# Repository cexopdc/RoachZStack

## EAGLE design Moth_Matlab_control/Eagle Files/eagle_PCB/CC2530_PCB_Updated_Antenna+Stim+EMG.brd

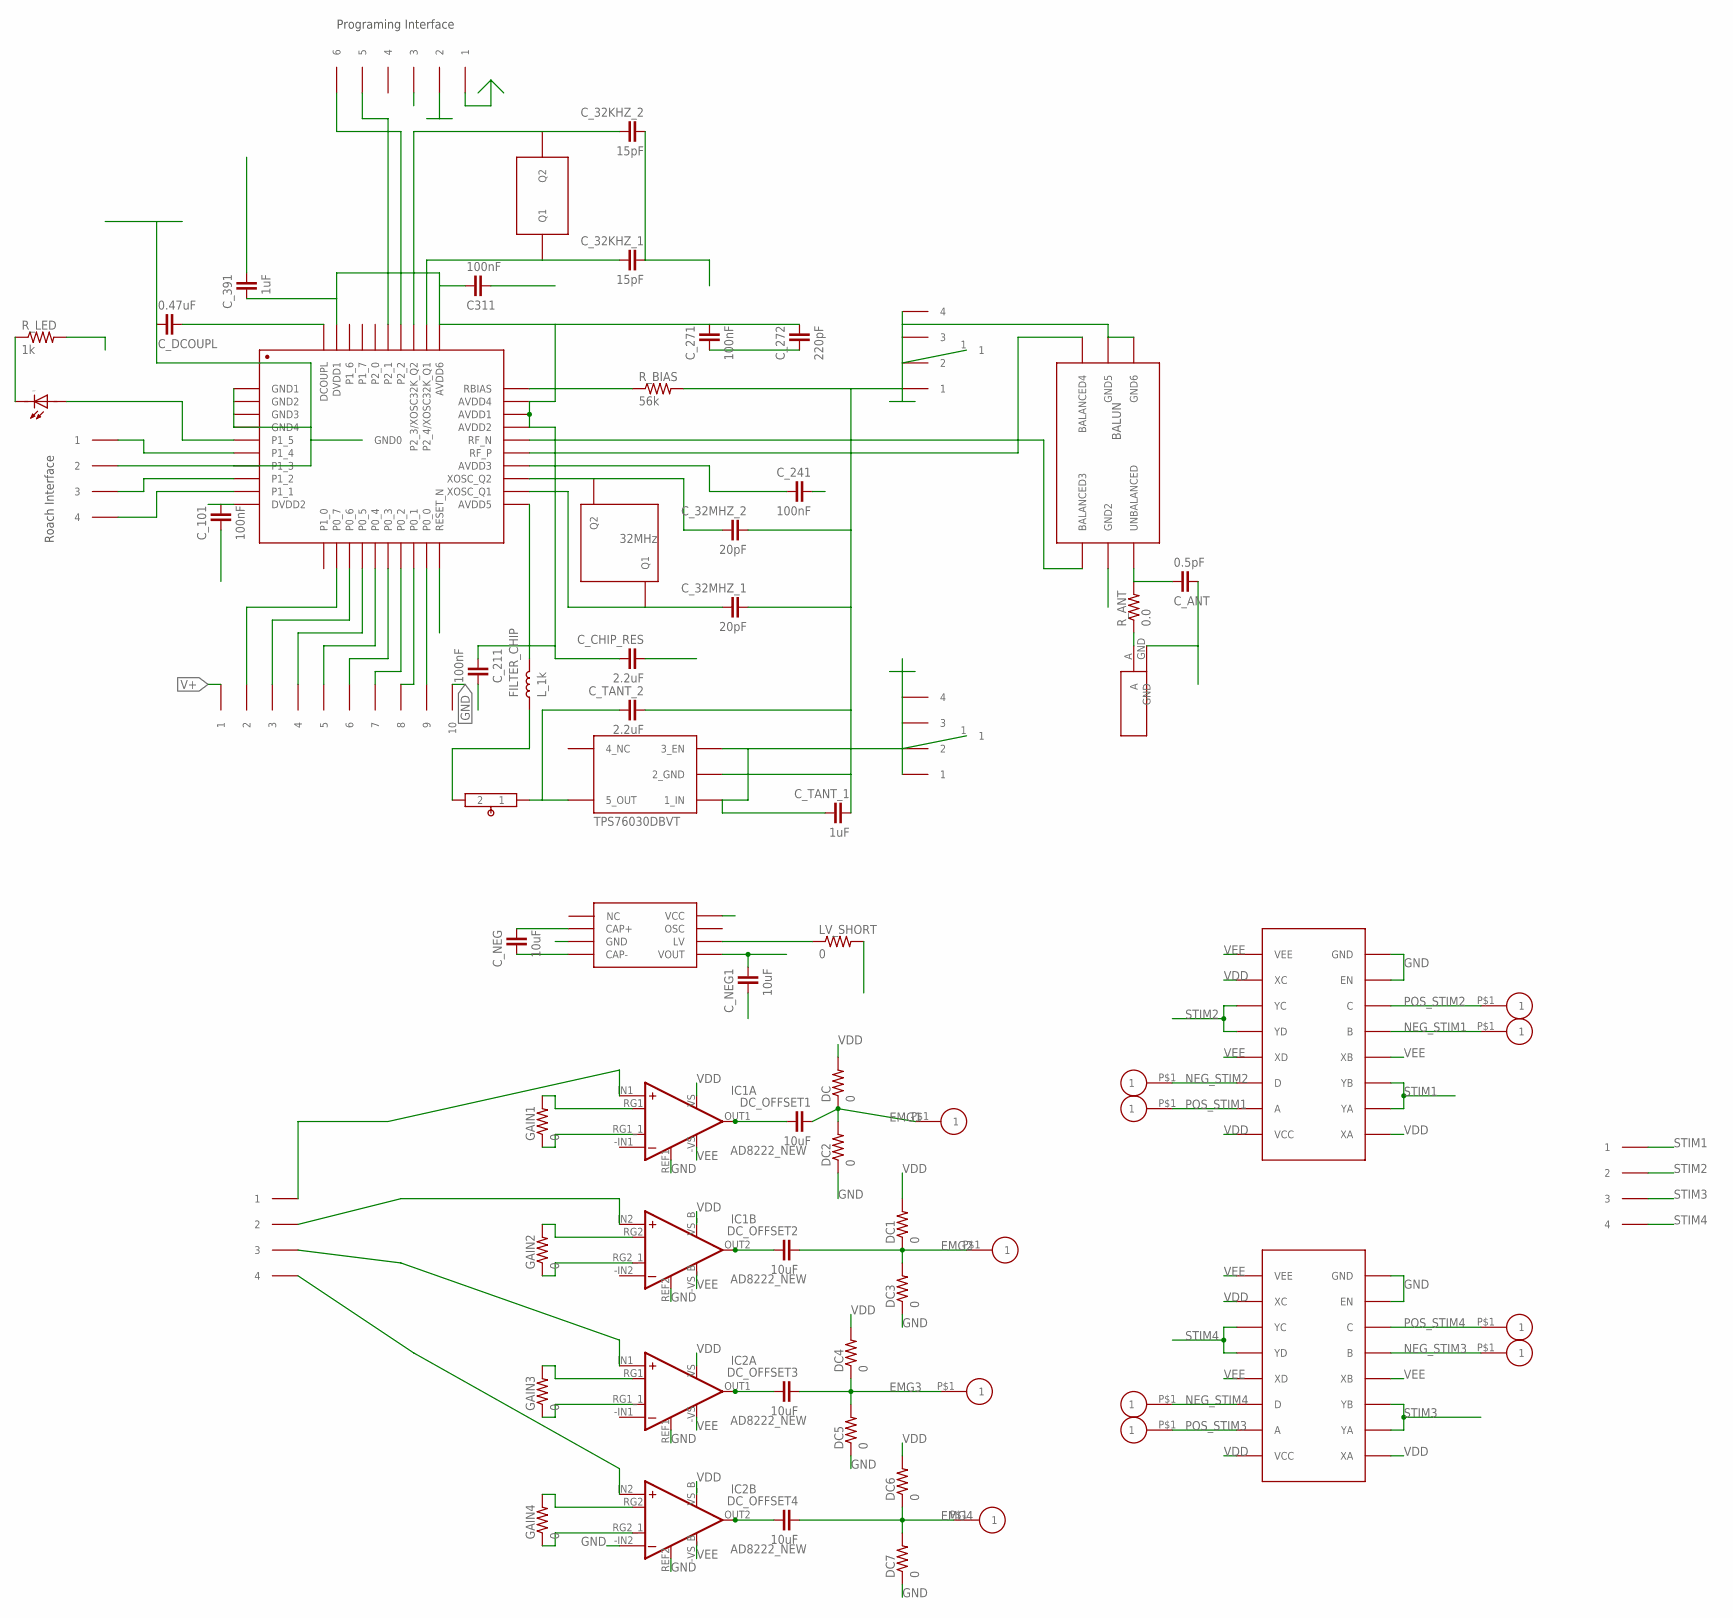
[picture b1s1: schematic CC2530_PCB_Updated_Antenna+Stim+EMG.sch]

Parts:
32KHZ: X32.768KHZ
C311: 100nF; 0201_R/L/C
C_32KHZ_1, C_32KHZ_2: 15pF; 0201_R/L/C
C_32MHZ_1, C_32MHZ_2: 20pF; 0201_R/L/C
C_101, C_211, C_241, C_271: 100nF; 0201_R/L/C
C_272: 220pF; 0201_R/L/C
C_391: 1uF; 0201_R/L/C
C_ANT: 0.5pF; 0201_R/L/C
C_CHIP_RES: 2.2uF; 0402_R/L/C
C_DCOUPL: 0.47uF; 0201_R/L/C
C_NEG, C_NEG1: 10uF; 0402_R/L/C
C_TANT_1: 1uF; 0603_R/L/C
C_TANT_2: 2.2uF; 0603_R/L/C
DC, DC1, DC2, DC3, DC4, DC5, DC6, DC7: 0; 0402_R/L/C
DC_OFFSET1, DC_OFFSET2, DC_OFFSET3, DC_OFFSET4: 10uF; 0402_R/L/C
EMG1: DBG_ELECTRODE
FILTER_CHIP: L_1k; 0402_R/L/C
GAIN1, GAIN2, GAIN3, GAIN4: 0; 0402_R/L/C
GND_IN: FFC4POS
IC1, IC2: AD8222_NEW; QFN-16
INVERTED_F-ANTENNA: ANTENNA
LED: LED0603; 0603_R/L/C
LV_SHORT: 0; 0402_R/L/C
R_ANT: 0.0; 0201_R/L/C
R_BIAS: 56k; 0201_R/L/C
R_LED: 1k; 0402_R/L/C
U$1: CC2530
U$2: BALUN
U$3: X32MHZ
U$4: TL7660; S-PDSO-G8
U$5, U$6: MC74HC4316A; SOIC-16-ON-SEMI
U$9, U$11, U$12, U$14, U$16, U$19, U$22, U$23, U$25, U$26, U$27: DBG_ELECTRODE
U$10: REGULATOR
U$13, U$24, U$28: FFC4POS
U$15: FFC10POS
U$17: FFC6POS
U$18: SWITCH_MANUAL
V+_IN: FFC4POS
WIRE+: DRILL_CONNECT
WIRE-: DRILL_CONNECT

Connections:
DCOUPL1: C_DCOUPL.1, U$1.DCOUPL
EMG1: DC.1, DC2.2, DC_OFFSET1.2, EMG1.P$1
EMG2: DC1.1, DC3.2, DC_OFFSET2.2, U$25.P$1
EMG3: DC4.1, DC5.2, DC_OFFSET3.2, U$26.P$1
EMG4: DC6.1, DC7.2, DC_OFFSET4.2, U$27.P$1
GND: C311.1, C_32KHZ_1.2, C_32KHZ_2.2, C_32MHZ_1.2, C_32MHZ_2.2, C_101.1, C_211.2, C_241.2, C_271.1, C_272.1, C_391.2, C_ANT.1, C_CHIP_RES.2, C_DCOUPL.2, C_NEG1.1, C_TANT_1.2, C_TANT_2.2, DC2.1, DC3.1, DC5.1, DC7.1, GND_IN.1, GND_IN.2, GND_IN.3, GND_IN.4, IC1.REF1 (REF), IC1.REF2 (REF), IC2.-IN2 (-IN), IC2.REF1 (REF), IC2.REF2 (REF), INVERTED_F-ANTENNA.GND, LV_SHORT.2, R_BIAS.2, R_LED.2, U$1.GND0, U$1.GND1, U$1.GND001 (GND0), U$1.GND2, U$1.GND002 (GND0), U$1.GND3, U$1.GND003 (GND0), U$1.GND4, U$1.GND004 (GND0), U$1.GND005 (GND0), U$1.GND006 (GND0), U$1.GND007 (GND0), U$1.GND008 (GND0), U$1.GND009 (GND0), U$1.GND010 (GND0), U$1.GND011 (GND0), U$1.GND012 (GND0), U$1.GND013 (GND0), U$1.GND014 (GND0), U$1.GND015 (GND0), U$1.GND016 (GND0), U$1.P1_3, U$2.GND2, U$2.GND5, U$2.GND6, U$4.3 (GND), U$5.7 (EN), U$5.8 (GND), U$6.7 (EN), U$6.8 (GND), U$10.2 (2_GND), U$13.2, U$15.10, U$17.2, WIRE-.1
LED/P1_5: LED.1 (A), U$1.P1_5
LT/P1_4: U$1.P1_4, U$13.1
unnamed: C_ANT.2, R_ANT.2, U$2.UNBALANCED
unnamed: INVERTED_F-ANTENNA.A, R_ANT.1
unnamed: C_NEG.2, U$4.2 (CAP+)
unnamed: C_NEG.1, U$4.4 (CAP-)
unnamed: LV_SHORT.1, U$4.6 (LV)
unnamed: GAIN1.2, IC1.RG1
unnamed: GAIN1.1, IC1.RG1_1
unnamed: GAIN2.2, IC1.RG2 (RG1)
unnamed: GAIN2.1, IC1.RG2_1 (RG1_1)
unnamed: GAIN3.2, IC2.RG1
unnamed: GAIN3.1, IC2.RG1_1
unnamed: GAIN4.2, IC2.RG2 (RG1)
unnamed: GAIN4.1, IC2.RG2_1 (RG1_1)
unnamed: DC_OFFSET1.1, IC1.OUT1 (OUT)
unnamed: DC_OFFSET2.1, IC1.OUT2 (OUT)
unnamed: DC_OFFSET4.1, IC2.OUT2 (OUT)
unnamed: DC_OFFSET3.1, IC2.OUT1 (OUT)
unnamed: IC2.IN2 (+IN), U$24.4
unnamed: IC2.IN1 (+IN), U$24.3
unnamed: IC1.IN2 (+IN), U$24.2
unnamed: C_TANT_2.1, U$10.5 (5_OUT), U$18.1
unnamed: IC1.IN1 (+IN), U$24.1
unnamed: LED.2 (C), R_LED.1
NC: U$4.1 (NC)
NEG_STIM1: U$5.5 (B), U$14.P$1
NEG_STIM2: U$5.14 (D), U$9.P$1
NEG_STIM3: U$6.5 (B), U$19.P$1
NEG_STIM4: U$6.14 (D), U$22.P$1
OSC: U$4.7 (OSC)
P0_0: U$1.P0_0, U$15.9
P0_1: U$1.P0_1, U$15.8
P0_2: U$1.P0_2, U$15.7
P0_3: U$1.P0_3, U$15.6
P0_4: U$1.P0_4, U$15.5
P0_5: U$1.P0_5, U$15.4
P0_6: U$1.P0_6, U$15.3
P0_7: U$1.P0_7, U$15.2
P2_1: U$1.P2_1, U$17.5
P2_2: U$1.P2_2, U$17.6
P2_3/X32K_Q2: 32KHZ.Q2, C_32KHZ_2.1, U$1.P2_3/XOSC32K_Q2
P2_4/X32K_Q1: 32KHZ.Q1, C_32KHZ_1.1, U$1.P2_4/XOSC32K_Q1
POS_STIM1: U$5.15 (A), U$11.P$1
POS_STIM2: U$5.6 (C), U$12.P$1
POS_STIM3: U$6.15 (A), U$23.P$1
POS_STIM4: U$6.6 (C), U$16.P$1
RBIAS: R_BIAS.1, U$1.RBIAS
RESET: U$1.RESET_N, U$17.3
RF_N: U$1.RF_N, U$2.BALANCED3
RF_P: U$1.RF_P, U$2.BALANCED4
RT/P1_2: U$1.P1_2, U$13.3
STIM1: U$5.2 (YA), U$5.3 (YB), U$28.1
STIM2: U$5.11 (YC), U$5.12 (YD), U$28.2
STIM3: U$6.2 (YA), U$6.3 (YB), U$28.3
STIM4: U$6.11 (YC), U$6.12 (YD), U$28.4
SWITCH_OUT: FILTER_CHIP.1, U$18.2
UP/P1_1: U$1.P1_1, U$13.4
V+: C_TANT_1.1, U$10.1 (1_IN), U$10.3 (3_EN), U$15.1, V+_IN.1, V+_IN.2, V+_IN.3, V+_IN.4, WIRE+.1
VDD: C311.2, C_101.2, C_211.1, C_241.1, C_271.2, C_272.2, C_391.1, C_CHIP_RES.1, DC.2, DC1.2, DC4.2, DC6.2, FILTER_CHIP.2, IC1.VS (V+), IC1.VS_B (V+), IC2.VS (V+), IC2.VS_B (V+), U$1.AVDD1, U$1.AVDD2, U$1.AVDD3, U$1.AVDD4, U$1.AVDD5, U$1.AVDD6, U$1.DVDD1, U$1.DVDD2, U$4.8 (VCC), U$5.1 (XA), U$5.10 (XC), U$5.16 (VCC), U$6.1 (XA), U$6.10 (XC), U$6.16 (VCC), U$17.1
VEE: C_NEG1.2, IC1.-VS (V-), IC1.-VS_B (V-), IC2.-VS (V-), IC2.-VS_B (V-), U$4.5 (VOUT), U$5.4 (XB), U$5.9 (VEE), U$5.13 (XD), U$6.4 (XB), U$6.9 (VEE), U$6.13 (XD)
X32M_Q1: C_32MHZ_1.1, U$1.XOSC_Q1, U$3.Q1
X32M_Q2: C_32MHZ_2.1, U$1.XOSC_Q2, U$3.Q2

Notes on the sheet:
Programing Interface
Roach Interface

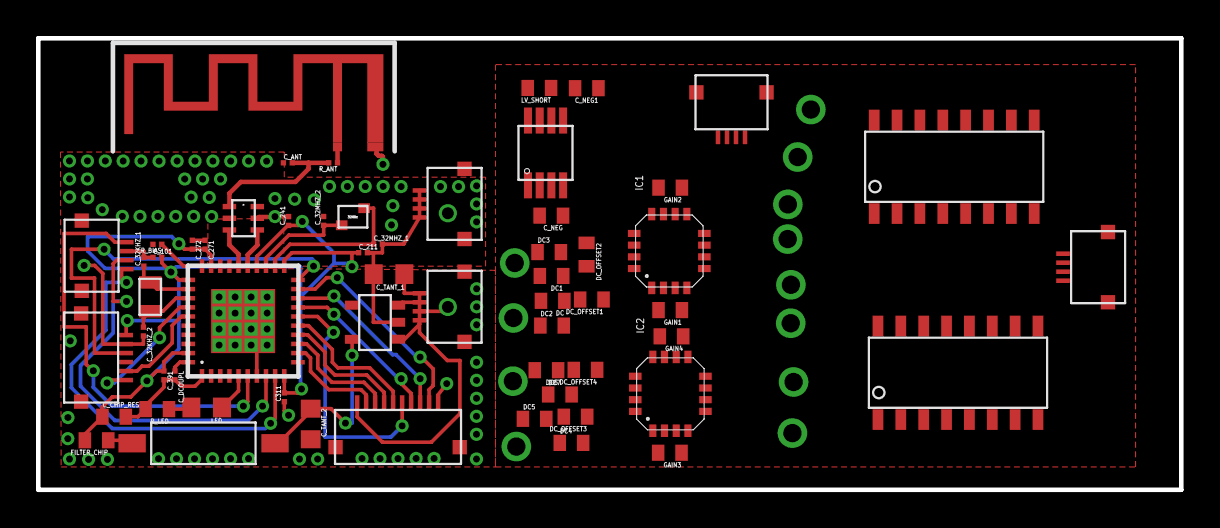
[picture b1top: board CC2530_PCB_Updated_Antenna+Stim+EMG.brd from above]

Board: 2 copper layers, 63.5 x 25.1 mm, 73 parts (0 on the bottom side), 67 nets.

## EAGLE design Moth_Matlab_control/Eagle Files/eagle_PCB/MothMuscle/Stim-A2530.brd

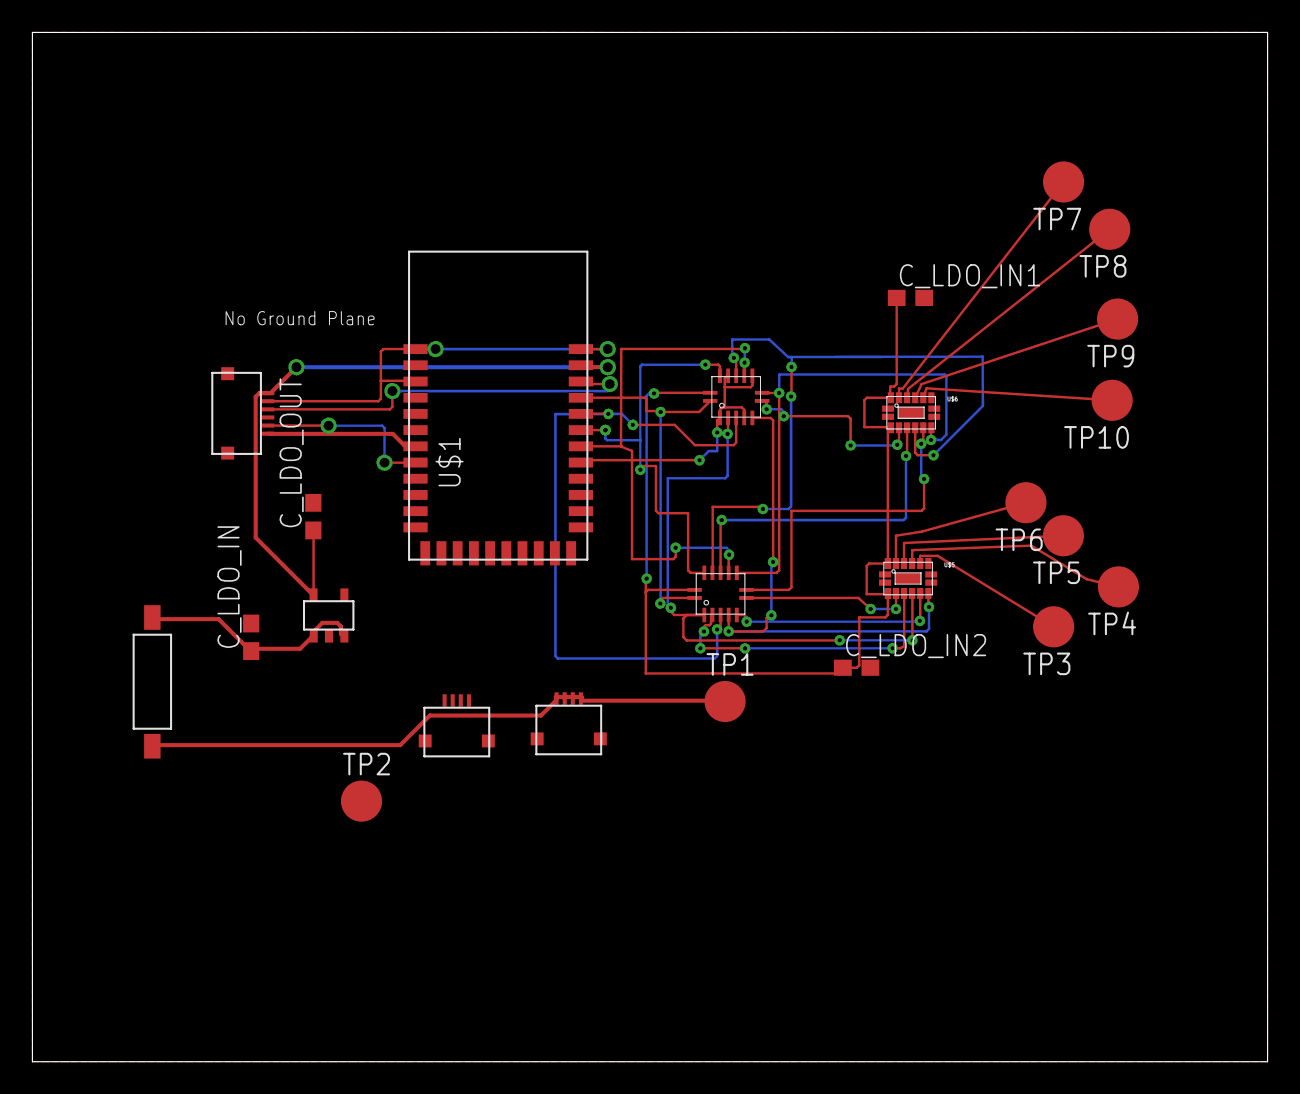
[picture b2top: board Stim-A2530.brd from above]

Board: 2 copper layers, 76.2 x 63.5 mm, 24 parts (0 on the bottom side), 29 nets.

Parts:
C_LDO_IN: 1uF; C0603
C_LDO_IN1, C_LDO_IN2: .1uF; C0603
C_LDO_OUT: 2.2uF; C0603
TP1, TP2, TP3, TP4, TP5, TP6, TP7, TP8, TP9, TP10: PTR1B2,54; B2,54
U$1: A2530
U$2: FFC6POS
U$3: AND_QUAD; QFN-14
U$4: XOR_QUAD; QFN-14
U$5, U$6: DRV8835; QFN-12-HEATSINK
U$7, U$8: FFC4POS
U$18: SWITCH_MANUAL
VREG1: REGULATOR

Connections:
+3V0: C_LDO_OUT.1, U$1.P$33, U$2.1, VREG1.5
+3V3: C_LDO_IN1.1, C_LDO_IN2.1, U$3.VCC, U$4.VCC, U$5.VCC, U$5.VM, U$6.VCC, U$6.VM
BCLK: U$1.P$27, U$3.B0, U$3.B1, U$3.B2, U$3.B3
GND: C_LDO_IN.2, C_LDO_IN1.2, C_LDO_IN2.2, C_LDO_OUT.2, TP2.TP, U$1.P$1, U$1.P$3, U$1.P$12, U$1.P$13, U$1.P$14, U$1.P$15, U$1.P$22, U$1.P$34, U$2.2, U$3.GND, U$4.GND, U$5.GND, U$5.MODE, U$6.GND, U$6.MODE, U$8.1, U$8.2, U$8.3, U$8.4, VREG1.2
unnamed: TP1.TP, U$7.1, U$7.2, U$7.3, U$7.4, U$18.1
unnamed: TP7.TP, U$6.AOUT1
unnamed: TP8.TP, U$6.AOUT2
unnamed: TP9.TP, U$6.BOUT1
unnamed: TP10.TP, U$6.BOUT2
unnamed: TP6.TP, U$5.AOUT1
unnamed: TP5.TP, U$5.AOUT2
unnamed: TP4.TP, U$5.BOUT1
unnamed: TP3.TP, U$5.BOUT2
NEG1: U$3.O_0, U$4.B0, U$5.AIN2.AENBL
NEG2: U$3.O1, U$4.B1, U$5.BIN2/BENBL
NEG3: U$3.O2, U$4.B2, U$6.AIN2.AENBL
NEG4: U$3.O3, U$4.B3, U$6.BIN2/BENBL
P1: U$1.P$31, U$3.A0, U$4.A0
P2: U$1.P$30, U$3.A1, U$4.A1
P2_1: U$1.P$8, U$2.5
P2_2: U$1.P$7, U$2.6
P3: U$1.P$29, U$3.A2, U$4.A2
P4: U$1.P$28, U$3.A3, U$4.A3
POS1: U$4.O_0, U$5.AIN1/APHASE
POS2: U$4.O1, U$5.BIN1/BPHASE
POS3: U$4.O2, U$6.AIN1/APHASE
POS4: U$4.O3, U$6.BIN1/BPHASE
RESET_N: U$1.P$32, U$2.3
V+: C_LDO_IN.1, U$18.2, VREG1.1, VREG1.3

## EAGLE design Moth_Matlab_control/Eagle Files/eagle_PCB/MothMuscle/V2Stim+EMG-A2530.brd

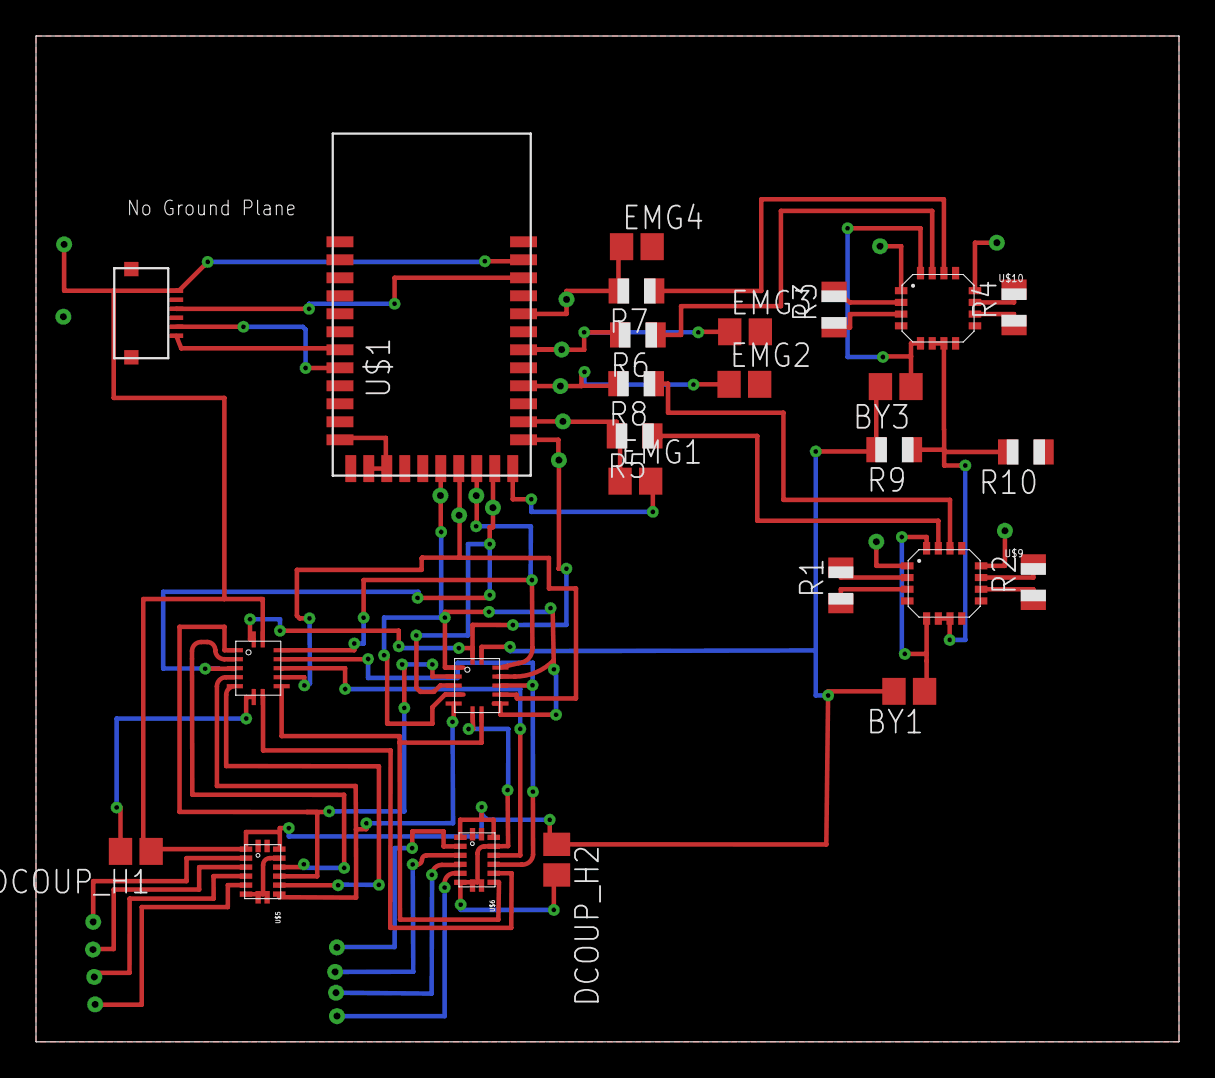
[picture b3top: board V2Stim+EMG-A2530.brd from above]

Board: 2 copper layers, 63.5 x 55.9 mm, 49 parts (0 on the bottom side), 49 nets.

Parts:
BY1, BY3: .1uF; C0805
DCOUP_H1, DCOUP_H2: .1uF; C0805
EMG1, EMG2, EMG3, EMG4: .1uF; C0805
R1, R2, R3, R4, R5, R6, R7, R8: 499; R0805
R9, R10: 10k; R0805
U$1: A2530
U$2: FFC6POS
U$3: AND_QUAD; QFN-14
U$4: XOR_QUAD; QFN-14
U$5, U$6: DRV8835; QFN-12-HEATSINK
U$7, U$8, U$11, U$12, U$13, U$14, U$15, U$16, U$17, U$18, U$19, U$20, U$21, U$22, U$23, U$24, U$25, U$26, U$27, U$28, U$29, U$30, U$31: DEBUG_PIN
U$9, U$10: AD8222; QFN-16

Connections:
+3V0: BY1.2, BY3.2, DCOUP_H1.1, DCOUP_H2.1, R9.2, U$1.P$33, U$2.1, U$3.VCC, U$4.VCC, U$5.VCC, U$5.VM, U$6.VCC, U$6.VM, U$26.P$1
A0: U$5.AOUT1, U$13.P$1
A1: U$5.AOUT2, U$14.P$1
B0: U$5.BOUT1, U$15.P$1
B1: U$5.BOUT2, U$16.P$1
BCLK: U$1.P$18, U$3.B0, U$3.B1, U$3.B2, U$3.B3, U$24.P$1
C0: U$6.AOUT1, U$17.P$1
C1: U$6.AOUT2, U$18.P$1
D0: U$6.BOUT1, U$19.P$1
D1: U$6.BOUT2, U$20.P$1
EMG1: EMG1.1, R5.2, U$1.P$24, U$31.P$1
EMG2: EMG2.1, R8.2, U$1.P$26, U$30.P$1
EMG3: EMG3.1, R6.2, U$1.P$28, U$29.P$1
EMG4: EMG4.1, R7.2, U$1.P$30, U$28.P$1
GND: DCOUP_H1.2, DCOUP_H2.2, EMG1.2, EMG2.2, EMG3.2, EMG4.2, R10.1, U$1.P$1, U$1.P$3, U$1.P$12, U$1.P$13, U$1.P$14, U$1.P$15, U$1.P$22, U$1.P$34, U$2.2, U$3.GND, U$4.GND, U$5.GND, U$5.MODE, U$6.GND, U$6.MODE, U$9.-VS, U$9.-VS_B, U$9.IN1, U$9.IN2, U$10.-VS, U$10.-VS_B, U$10.IN1, U$10.IN2, U$27.P$1
IN1: U$7.P$1, U$9.-IN1
IN2: U$8.P$1, U$9.-IN2
IN3: U$10.-IN1, U$11.P$1
IN4: U$10.-IN2, U$12.P$1
unnamed: R1.2, U$9.RG1
unnamed: R1.1, U$9.RG1_B
unnamed: R2.2, U$9.RG2
unnamed: R2.1, U$9.RG2_B
unnamed: R3.2, U$10.RG1
unnamed: R3.1, U$10.RG1_B
unnamed: R4.2, U$10.RG2
unnamed: R4.1, U$10.RG2_B
unnamed: R5.1, U$9.OUT1
unnamed: R8.1, U$9.OUT2
unnamed: R6.1, U$10.OUT1
unnamed: R7.1, U$10.OUT2
unnamed: BY3.1, U$10.VS, U$10.VS_B
unnamed: BY1.1, U$9.VS, U$9.VS_B
NEG1: U$3.O_0, U$4.B0, U$5.AIN2
NEG2: U$3.O1, U$4.B1, U$5.BIN2
NEG3: U$3.O2, U$4.B2, U$6.AIN2
NEG4: U$3.O3, U$4.B3, U$6.BIN2
P1: U$1.P$23, U$3.A0, U$4.A0, U$21.P$1
P2: U$1.P$21, U$3.A1, U$4.A1, U$25.P$1
P2_1: U$1.P$8, U$2.5
P2_2: U$1.P$7, U$2.6
P3: U$1.P$20, U$3.A2, U$4.A2, U$22.P$1
P4: U$1.P$19, U$3.A3, U$4.A3, U$23.P$1
POS1: U$4.O_0, U$5.AIN1
POS2: U$4.O1, U$5.BIN1
POS3: U$4.O2, U$6.AIN1
POS4: U$4.O3, U$6.BIN1
REF: R9.1, R10.2, U$9.REF1, U$9.REF2, U$10.REF1, U$10.REF2
RESET_N: U$1.P$32, U$2.3
